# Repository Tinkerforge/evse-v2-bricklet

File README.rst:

EVSE Bricklet 2.0
=================

This Bricklet together with the ESP32 Ethernet Brick and the NFC Bricklet
form the hardware used in the WARP2 Charger.

The Firmware for the EVSE Bricklet 2.0 is also used for the EVSE Bricklet 3.0:
https://github.com/Tinkerforge/evse-v3-bricklet. The hardware version is
run-time detected.

See https://www.warp-charger.com/ for more details about WARP Charger.

This repository contains the firmware source code and the hardware design
files. The documentation generator configs can be found at
https://github.com/Tinkerforge/generators

.. BEGIN WARP REPOSITORIES (managed block, generated from esp32-firmware/repo_overview.rst - do not edit by hand, run update_repo_overview.py instead)

WARP Repositories
-----------------

This is an overview of all repositories that make up the WARP Charger and
WARP Energy Manager ecosystem.

Please report **any** issue concerning WARP hard- or software in the
`esp32-firmware`_ repository, no matter which repository it originates from.

Software
~~~~~~~~

- `esp32-firmware`_ - Source code of the ESP32 firmware shared between all WARP Chargers and Energy Managers

Libraries used by the firmware:

- `tfjson`_ - SAX style JSON serializer and deserializer
- `tfnetwork`_ - Modbus TCP server and client implementation
- `tfocpp`_ - OCPP 1.6 implementation
- `tftools`_ - Miscellaneous tools and helpers

Remote access:

- `esp32-remote-access`_ - Source code of the my.warp-charger.com remote access server

Documentation, tools and integrations:

- `warp-charger`_ - Source code of (docs.)warp-charger.com and the printed manual, released firmwares, datasheets and documents, as well as some tools and hardware design files
- `api.warp-charger.com`_ - Serves APIs that are used by WARP Chargers to obtain relevant public information like day ahead prices
- `vislog.warp-charger.com`_ - Visualizes WARP Charger logs and EVSE debug protocols
- `dbus-warp-charger`_ - Integrates WARP Chargers into a Victron Energy Venus OS device (e.g. Cerbo GX)

WARP Charger Hardware
~~~~~~~~~~~~~~~~~~~~~~

WARP4 Charger
"""""""""""""

*Current charger generation.*

- `warp-esp32-ethernet-v2-brick`_ - Hardware design files of the WARP ESP32 Ethernet Brick 2.0
- `warp-esp32-ethernet-v2-co-bricklet`_ - Firmware source code of the WARP ESP32 Ethernet 2.0 Co Bricklet (co-processor)
- `evse-v4-bricklet`_ - Hardware design files of the EVSE 4.0 Bricklet (firmware shared with the EVSE 2.0 Bricklet)
- `nfc-bricklet`_ - Firmware source code and hardware design files of the NFC Bricklet

WARP3 Charger
"""""""""""""

- `warp-esp32-ethernet-brick`_ - Hardware design files of the WARP ESP32 Ethernet Brick
- `evse-v3-bricklet`_ - Hardware design files of the EVSE 3.0 Bricklet (firmware shared with the EVSE 2.0 Bricklet)
- `nfc-bricklet`_ - Firmware source code and hardware design files of the NFC Bricklet

WARP2 Charger
"""""""""""""

- `esp32-ethernet-brick`_ - Hardware design files of the ESP32 Ethernet Brick
- `evse-v2-bricklet`_ - Firmware source code and hardware design files of the EVSE 2.0 Bricklet
- `nfc-bricklet`_ - Firmware source code and hardware design files of the NFC Bricklet

WARP1 Charger
"""""""""""""

- `esp32-brick`_ - Hardware design files of the ESP32 Brick
- `evse-bricklet`_ - Firmware source code and hardware design files of the EVSE Bricklet
- `rs485-bricklet`_ - Firmware source code and hardware design files of the RS485 Bricklet

WARP Energy Manager Hardware
~~~~~~~~~~~~~~~~~~~~~~~~~~~~~~

WARP Energy Manager 2.0
"""""""""""""""""""""""

*Current energy manager generation.*

- `esp32-ethernet-brick`_ - Hardware design files of the ESP32 Ethernet Brick
- `warp-energy-manager-v2-bricklet`_ - Firmware source code and hardware design files of the WARP Energy Manager 2.0 Bricklet
- `warp-front-panel-bricklet`_ - Firmware source code and hardware design files of the WARP Front Panel Bricklet

WARP Energy Manager 1.0
"""""""""""""""""""""""

- `esp32-ethernet-brick`_ - Hardware design files of the ESP32 Ethernet Brick
- `warp-energy-manager-bricklet`_ - Firmware source code and hardware design files of the WARP Energy Manager Bricklet

Forked/patched projects
~~~~~~~~~~~~~~~~~~~~~~~~~

- `arduino-esp32`_
- `esp32-arduino-libs`_
- `WireGuard-ESP32-Arduino`_

.. Link targets: One definition per repository, keep in sync with the lists above.

.. _esp32-firmware: https://github.com/Tinkerforge/esp32-firmware
.. _tfjson: https://github.com/Tinkerforge/tfjson
.. _tfnetwork: https://github.com/Tinkerforge/tfnetwork
.. _tfocpp: https://github.com/Tinkerforge/tfocpp
.. _tftools: https://github.com/Tinkerforge/tftools
.. _esp32-remote-access: https://github.com/Tinkerforge/esp32-remote-access
.. _warp-charger: https://github.com/Tinkerforge/warp-charger
.. _api.warp-charger.com: https://github.com/Tinkerforge/api.warp-charger.com
.. _vislog.warp-charger.com: https://github.com/Tinkerforge/vislog.warp-charger.com
.. _dbus-warp-charger: https://github.com/Tinkerforge/dbus-warp-charger
.. _warp-esp32-ethernet-v2-brick: https://github.com/Tinkerforge/warp-esp32-ethernet-v2-brick
.. _warp-esp32-ethernet-v2-co-bricklet: https://github.com/Tinkerforge/warp-esp32-ethernet-v2-co-bricklet
.. _evse-v4-bricklet: https://github.com/Tinkerforge/evse-v4-bricklet
.. _nfc-bricklet: https://github.com/Tinkerforge/nfc-bricklet
.. _warp-esp32-ethernet-brick: https://github.com/Tinkerforge/warp-esp32-ethernet-brick
.. _evse-v3-bricklet: https://github.com/Tinkerforge/evse-v3-bricklet
.. _esp32-ethernet-brick: https://github.com/Tinkerforge/esp32-ethernet-brick
.. _evse-v2-bricklet: https://github.com/Tinkerforge/evse-v2-bricklet
.. _esp32-brick: https://github.com/Tinkerforge/esp32-brick
.. _evse-bricklet: https://github.com/Tinkerforge/evse-bricklet
.. _rs485-bricklet: https://github.com/Tinkerforge/rs485-bricklet
.. _warp-energy-manager-v2-bricklet: https://github.com/Tinkerforge/warp-energy-manager-v2-bricklet
.. _warp-front-panel-bricklet: https://github.com/Tinkerforge/warp-front-panel-bricklet
.. _warp-energy-manager-bricklet: https://github.com/Tinkerforge/warp-energy-manager-bricklet
.. _arduino-esp32: https://github.com/Tinkerforge/arduino-esp32
.. _esp32-arduino-libs: https://github.com/Tinkerforge/esp32-arduino-libs
.. _WireGuard-ESP32-Arduino: https://github.com/Tinkerforge/WireGuard-ESP32-Arduino

.. END WARP REPOSITORIES

Repository Content
------------------

software/:
 * examples/: Examples for all supported languages
 * build/: Compiled files
 * src/: Source code of firmware
 * Makefile: Makefile to build project

hardware/:
 * Contains KiCad project files and additionally schematics as PDF

datasheets/:
 * Contains datasheets for sensors and complex ICs that are used

Hardware
--------

The hardware is designed with the open source EDA Suite KiCad
(http://www.kicad.org). Before you are able to open the files,
you have to install the Tinkerforge kicad-libraries
(https://github.com/Tinkerforge/kicad-libraries). You can either clone
them directly in hardware/ or clone them in a separate folder and
symlink them into hardware/
(ln -s kicad_path/kicad-libraries project_path/hardware). After that you
can open the .pro file in hardware/ with KiCad and from there view and
modify the schematics and the PCB layout.

Software
--------

If you want to do your own Brick/Bricklet firmware development we highly
recommend that you use our build environment setup script and read the
tutorial (https://www.tinkerforge.com/en/doc/Tutorials/Tutorial_Build_Environment/Tutorial.html).

To compile the C code we recommend you to install the newest GNU Arm Embedded
Toolchain (https://launchpad.net/gcc-arm-embedded/+download).
You also need to install bricklib2 (https://github.com/Tinkerforge/bricklib2).

You can either clone it directly in software/src/ or clone it in a
separate folder and symlink it into software/src/
(ln -s bricklib_path/bricklib2 project_path/software/src/). Finally make sure to
have CMake installed (http://www.cmake.org/cmake/resources/software.html).

After that you can build the firmware by invoking make in software/.
The firmware (.zbin) can then be found in software/build/ and uploaded
with brickv (click button "Flashing" on start screen).

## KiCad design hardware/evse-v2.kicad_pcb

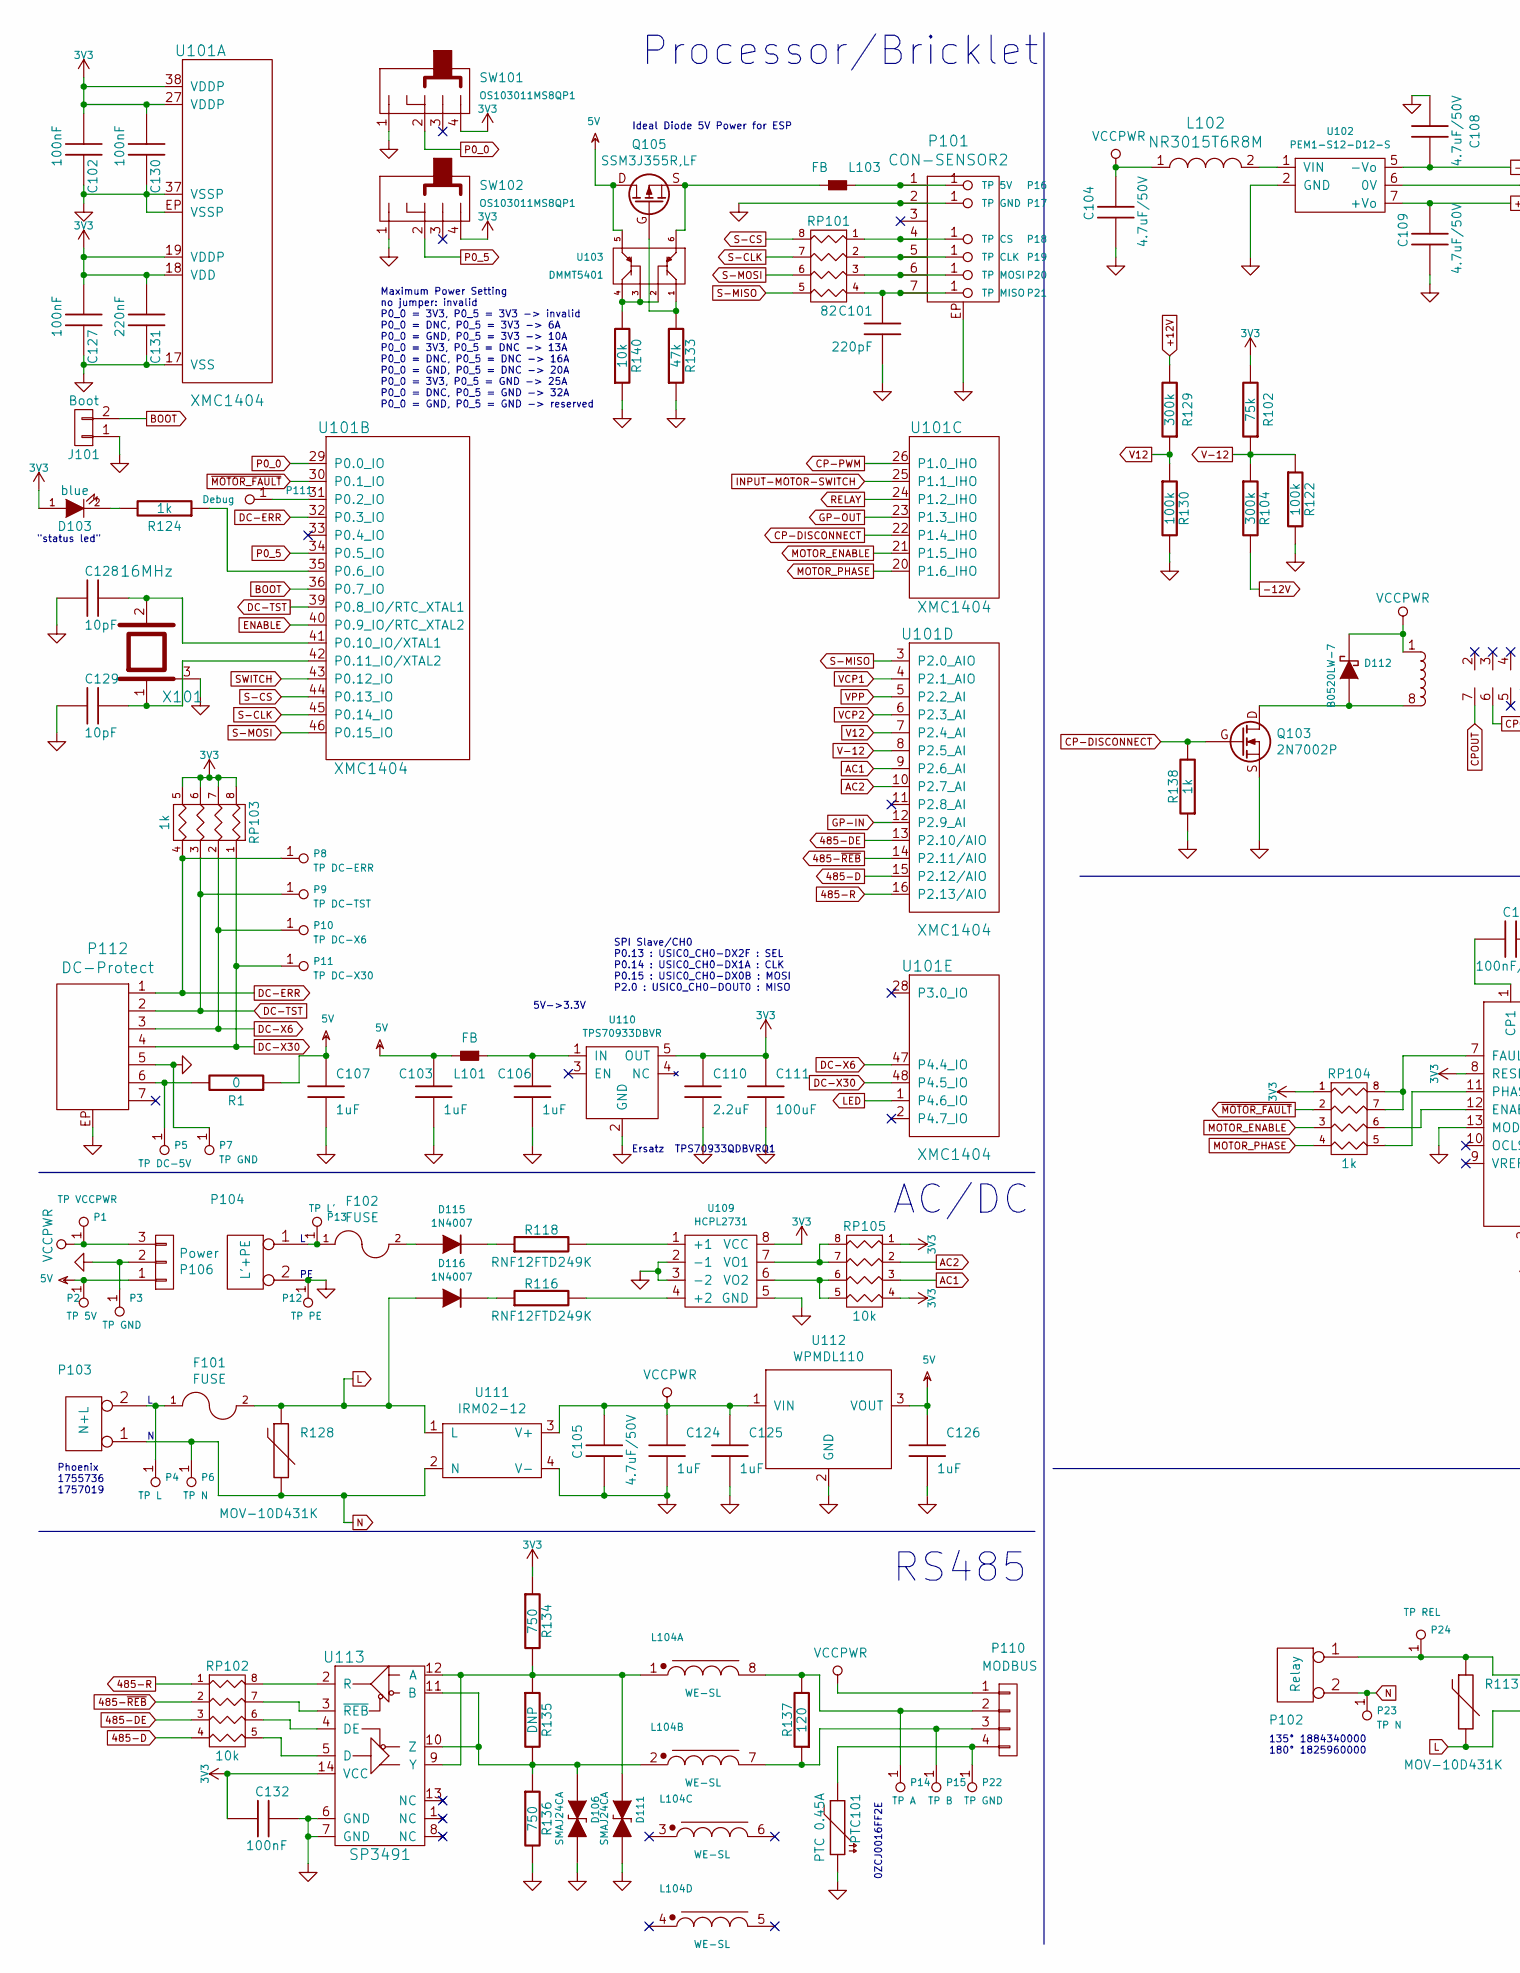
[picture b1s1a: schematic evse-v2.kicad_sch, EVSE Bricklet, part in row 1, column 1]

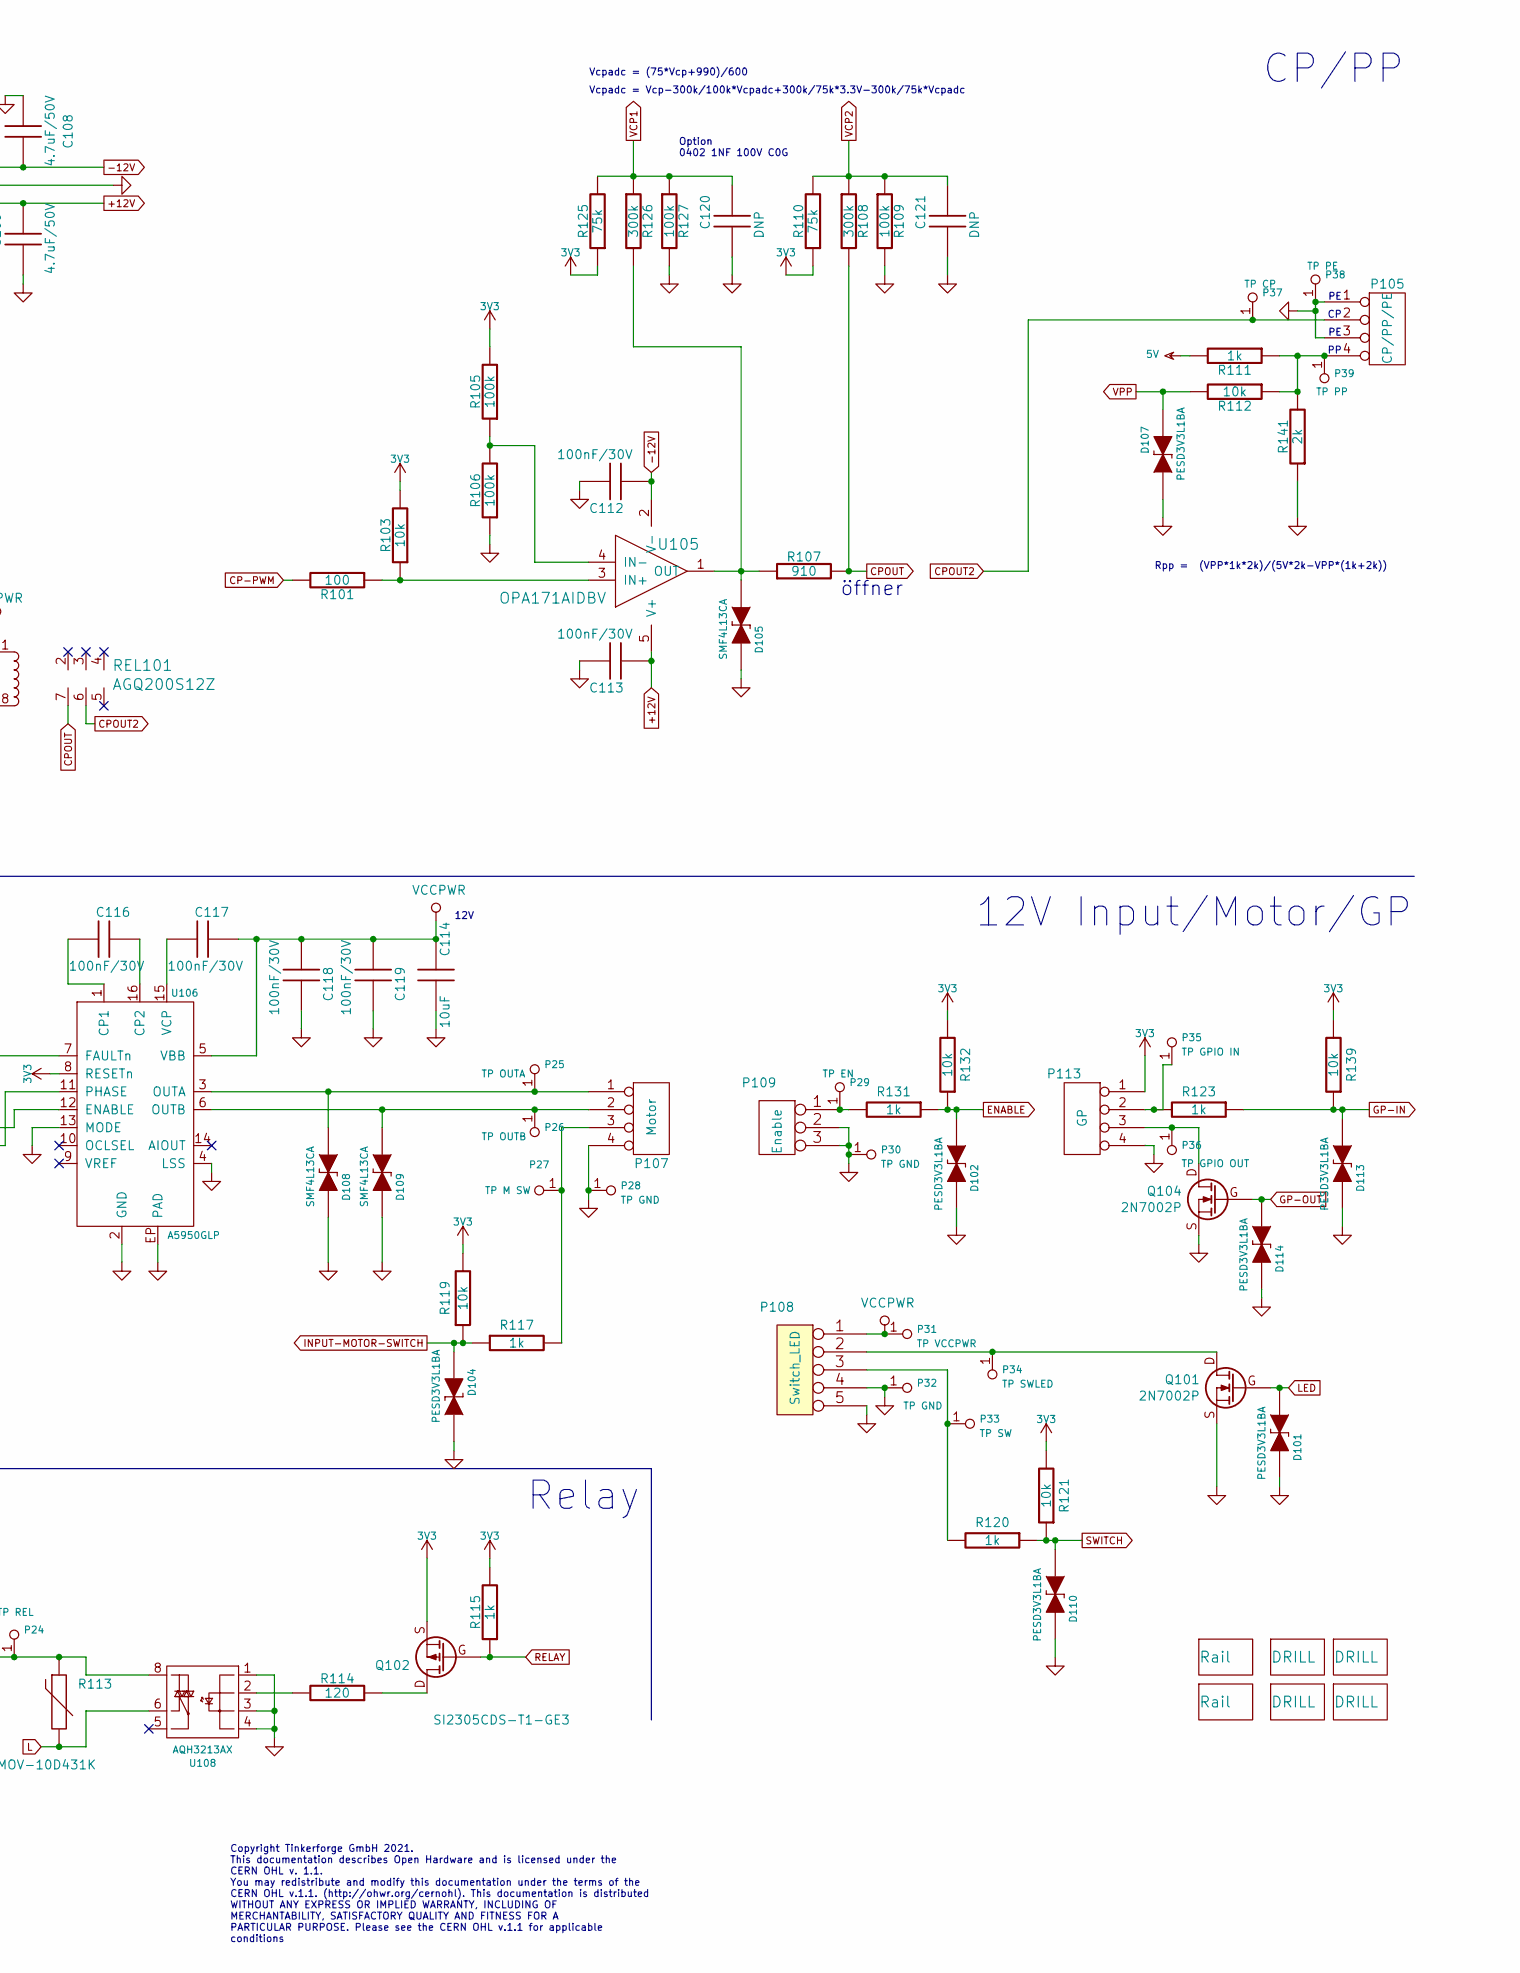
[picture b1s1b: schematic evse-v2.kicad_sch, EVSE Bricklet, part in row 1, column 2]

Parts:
A101, A102, A103, A104: DRILL; DRILL_NP_35
A105, A106: Rail; din-rail-mount
C101: 220pF; C0402F
C102, C127, C130, C132: 100nF; C0603F
C103, C106, C107, C124, C125, C126: 1uF; C0603F
C104, C105, C108, C109: 4.7uF/50V; C1206
C110: 2.2uF; C0603F
C111: 100uF; C1210
C112, C113, C116, C117, C118, C119: 100nF/30V; C0603F
C114: 10uF; C1206
C120, C121: DNP; C0402F
C128, C129: 10pF; C0603F
C131: 220nF; C0603F
D101, D102, D104, D107, D110, D113, D114: ‎PESD3V3L1BA; SOD-323
D103: blue; D0603F
D105, D108, D109: SMF4L13CA; SOD-123FL
D106, D111: SMAJ24CA; DO-214AC
D112: B0520LW-7; SOD-123
D115, D116: 1N4007; DO-41
F101, F102: FUSE; Fuse-Holder-5x20
J101: Boot; SolderJumper
L101, L103: FB; R0603F
L102: NR3015T6R8M; NR3030
L104: WE-SL
P1, P31: TP VCCPWR; TSTPT
P2, P16: TP 5V; TSTPT
P3, P7, P17, P22, P28, P30, P32: TP GND; TSTPT
P4: TP L; TSTPT
P5: TP DC-5V; TSTPT
P6, P23: TP N; TSTPT
P8: TP DC-ERR; TSTPT
P9: TP DC-TST; TSTPT
P10: TP DC-X6; TSTPT
P11: TP DC-X30; TSTPT
P12, P38: TP PE; TSTPT
P13: TP L'; TSTPT
P14: TP A; TSTPT
P15: TP B; TSTPT
P18: TP CS; TSTPT
P19: TP CLK; TSTPT
P20: TP MOSI; TSTPT
P21: TP MISO; TSTPT
P24: TP REL; TSTPT
P25: TP OUTA; TSTPT
P26: TP OUTB; TSTPT
P27: TP M SW; TSTPT
P29: TP EN; TSTPT
P33: TP SW; TSTPT
P34: TP SWLED; TSTPT
P35: TP GPIO IN; TSTPT
P36: TP GPIO OUT; TSTPT
P37: TP CP; TSTPT
P39: TP PP; TSTPT
P101: CON-SENSOR2; CON-SENSOR2_180
P102: Relay; LSF-SMT-500-02-135
P103: N+L; wm_2491620000
P104: L'+PE; wm_2491620000
P105: CP/PP/PE; OQ_4P_Vertical
P106: Power; JST-PH-3-THT
P107: Motor; JST-PH-4-THT
P108: Switch_LED; JST-PH-5-THT
P109: Enable; JST-PH-3-THT
P110: MODBUS; JST-PH-4-THT
P111: Debug; DEBUG_PAD
P112: DC-Protect; CON-SENSOR2_180
P113: GP; JST-PH-4-THT
PTC101: PTC 0.45A; C1206
Q101, Q103, Q104: 2N7002P; SOT23GDS
Q102: SI2305CDS-T1-GE3; SOT23GDS
Q105: SSM3J355R,LF; SOT23GDS
R1: 0; R1210
R101: 100; R0603F
R102, R110, R125: 75k; R0603F
R103, R112, R119, R121, R132, R139, R140: 10k; R0603F
R104, R108, R126, R129: 300k; R0603F
R105, R106, R109, R122, R127, R130: 100k; R0603F
R107: 910; R0603F
R111, R115, R117, R120, R123, R124, R131, R138: 1k; R0603F
R113, R128: MOV-10D431K; VAR_10mm
R114, R137: 120; R0805E
R116, R118: RNF12FTD249K; RNF12-2
R133: 47k; R0603F
R134, R136: 750; R0603F
R135: DNP; R0603F
R141: 2k; R0603F
REL101: AGQ200S12Z; AGQ2X0
RP101: 82; 4X0402
RP102: 10k; 0603X4
RP103, RP104: 1k; 4X0603
RP105: 10k; 4X0603
SW101, SW102: OS103011MS8QP1
U101: XMC1404; QFN48-EP2
U102: PEM1-S12-D12-S; PEM1S
U103: DMMT5401; SOT26
U105: OPA171AIDBV; SOT23-5
U106: A5950GLP; TSSOP16_EP
U108: AQH3213AX; AQ-H
U109: HCPL2731; DIP-8
U110: TPS70933DBVR; SOT23-5
U111: IRM02-12; IRM02
U112: WPMDL110
U113: SP3491; SOIC-14_3.9x8.7mm_Pitch1.27mm
X101: 16MHz; CRYSTAL_3225

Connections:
3V3: C102.1, C110.1, C111.1, C127.1, C130.1, C131.1, C132.2, D103.1 (A), P113.1, Q102.S, R102.2, R103.2, R105.2, R110.1, R115.2, R119.2, R121.2, R125.1, R132.2, R134.1, R139.2, RP103.5 (R4), RP103.6 (R3), RP103.7 (R2), RP103.8 (R1), RP104.1, RP105.1, RP105.4, SW101.4, SW102.4, U101.18 (VDD), U101.19 (VDDP), U101.27 (VDDP), U101.38 (VDDP), U106.8 (RESETn), U109.8 (VCC), U110.5 (OUT), U113.14 (VCC)
5V: C103.1, C107.1, C126.1, L101.2, P2.1, P106.1, Q105.D, R1.1, R111.2, U103.5, U112.3 (VOUT)
485-D: RP102.4, U101.15 (P2.12/AIO)
485-DE: RP102.3, U101.13 (P2.10/AIO)
485-R: RP102.1, U101.16 (P2.13/AIO)
485-~REB: RP102.2, U101.14 (P2.11/AIO)
+12V: C109.1, C113.2, R129.2, U102.7 (+Vo), U105.5 (V+)
-12V: C108.2, C112.2, R104.2, U102.5 (-Vo), U105.2 (V-)
AC1: RP105.3, U101.9 (P2.6_AI)
AC2: RP105.2, U101.10 (P2.7_AI)
BOOT: J101.2, U101.36 (P0.7_IO)
CP-DISCONNECT: Q103.G, R138.2, U101.22 (P1.4_IHO)
CP-PWM: R101.2, U101.26 (P1.0_IHO)
CPOUT: R107.2, R108.2, REL101.7
CPOUT2: P37.1, P105.2, REL101.6
DC-ERR: P8.1, P112.1, RP103.4, U101.32 (P0.3_IO)
DC-TST: P9.1, P112.2, RP103.3, U101.39 (P0.8_IO/RTC_XTAL1)
DC-X6: P10.1, P112.3, RP103.2, U101.47 (P4.4_IO)
DC-X30: P11.1, P112.4, RP103.1, U101.48 (P4.5_IO)
ENABLE: D102.1 (A), R131.1, R132.1, U101.40 (P0.9_IO/RTC_XTAL2)
GND: C101.2, C102.2, C103.2, C104.2, C105.2, C106.2, C107.2, C108.1, C109.2, C110.2, C111.2, C112.1, C113.1, C114.2, C118.1, C119.1, C120.2, C121.2, C124.2, C125.2, C126.2, C127.2, C128.2, C129.2, C130.2, C131.2, C132.1, D101.2 (K), D102.2 (K), D104.1 (A), D105.2 (K), D106.2 (K), D107.1 (A), D108.2 (K), D109.2 (K), D110.2 (K), D111.2 (K), D113.2 (K), D114.2 (K), J101.1, P3.1, P7.1, P12.1, P17.1, P28.1, P30.1, P32.1, P38.1, P101.2, P101.EP, P104.2 (PM), P105.1, P105.3, P106.2, P107.4, P108.4, P108.5, P109.2 (PM), P109.3, P112.5, P112.EP, P113.4, PTC101.2, Q101.S, Q103.S, Q104.S, R106.1, R109.2, R122.2, R127.2, R130.2, R133.1, R136.2, R138.1, R140.1, R141.1, SW101.1, SW102.1, U101.17 (VSS), U101.37 (VSSP), U101.EP (VSSP), U102.2 (GND), U102.6 (0V), U106.2 (GND), U106.4 (LSS), U106.13 (MODE), U106.EP (PAD), U108.1, U108.3, U108.4, U109.2 (-1), U109.3 (-2), U109.5 (GND), U110.2 (GND), U111.4 (V-), U112.2 (GND), U113.6 (GND), U113.7 (GND), X101.3
GP-IN: D113.1 (A), R123.1, R139.1, U101.12 (P2.9_AI)
GP-OUT: D114.1 (A), Q104.G, U101.23 (P1.3_IHO)
INPUT-MOTOR-SWITCH: D104.2 (K), R117.1, R119.1, U101.25 (P1.1_IHO)
L: D116.1 (A), F101.2, R113.2, R128.1, U108.6, U111.1 (L)
LED: D101.1 (A), Q101.G, U101.1 (P4.6_IO)
MOTOR_ENABLE: RP104.3, U101.21 (P1.5_IHO)
MOTOR_PHASE: RP104.4, U101.20 (P1.6_IHO)
N: P6.1, P23.1, P102.2 (PM), P103.1, R128.2, U111.2 (N)
unnamed: C101.1, P21.1, P101.7, RP101.4
unnamed: C106.1, L101.1, U110.1 (IN)
unnamed: C116.1, U106.16 (CP2)
unnamed: C116.2, U106.1 (CP1)
unnamed: C117.2, U106.15 (VCP)
unnamed: C128.1, U101.41 (P0.10_IO/XTAL1), X101.2
unnamed: C129.1, U101.42 (P0.11_IO/XTAL2), X101.1
unnamed: D103.2 (K), R124.2
unnamed: D105.1 (A), R107.1, R126.2, U105.1 (OUT)
unnamed: D106.1 (A), L104.2, R135.2, R136.1, U113.10 (Z), U113.11 (B)
unnamed: D108.1 (A), P25.1, P107.1, U106.3 (OUTA)
unnamed: D109.1 (A), P26.1, P107.2, U106.6 (OUTB)
unnamed: D111.1 (A), L104.1, R134.2, R135.1, U113.9 (Y), U113.12 (A)
unnamed: D112.1 (A), Q103.D, REL101.8
unnamed: D115.1 (A), F102.2
unnamed: D115.2 (K), R118.1
unnamed: D116.2 (K), R116.1
unnamed: F101.1, P4.1, P103.2 (PM)
unnamed: F102.1, P13.1, P104.1
unnamed: L102.2, U102.1 (VIN)
unnamed: L103.1, Q105.S, U103.6
unnamed: L103.2, P16.1, P101.1
unnamed: L104.7, P15.1, P110.3, R137.1
unnamed: L104.8, P14.1, P110.2, R137.2
unnamed: P18.1, P101.4, RP101.1
unnamed: P19.1, P101.5, RP101.2
unnamed: P20.1, P101.6, RP101.3
unnamed: P24.1, P102.1, R113.1, U108.8
unnamed: P39.1, P105.4, R111.1, R112.1, R141.2
unnamed: P27.1, P107.3, R117.2
unnamed: P34.1, P108.2, Q101.D
unnamed: P33.1, P108.3, R120.2
unnamed: P29.1, P109.1, R131.2
unnamed: P22.1, P110.4, PTC101.1
unnamed: P111.1, U101.31 (P0.2_IO)
unnamed: P5.1, P112.6, R1.2
unnamed: P35.1, P113.2, R123.2
unnamed: P36.1, P113.3, Q104.D
unnamed: Q102.D, R114.1
unnamed: Q105.G, R133.2, U103.1
unnamed: R101.1, R103.1, U105.3 (IN+)
unnamed: R105.1, R106.2, U105.4 (IN-)
unnamed: R114.2, U108.2
unnamed: R116.2, U109.4 (+2)
unnamed: R118.2, U109.1 (+1)
unnamed: R124.1, U101.35 (P0.6_IO)
unnamed: R140.2, U103.2, U103.3, U103.4
unnamed: RP102.5 (R4), U113.5 (D)
unnamed: RP102.6 (R3), U113.4 (DE)
unnamed: RP102.7 (R2), U113.3 (~REB)
unnamed: RP102.8 (R1), U113.2 (R)
unnamed: RP104.5 (R4), U106.11 (PHASE)
unnamed: RP104.6 (R3), U106.12 (ENABLE)
unnamed: RP104.7 (R2), RP104.8 (R1), U106.7 (FAULTn)
unnamed: RP105.5 (R4), RP105.6 (R3), U109.6 (VO2)
unnamed: RP105.7 (R2), RP105.8 (R1), U109.7 (VO1)
P0_0: SW101.2, U101.29 (P0.0_IO)
P0_5: SW102.2, U101.34 (P0.5_IO)
RELAY: Q102.G, R115.1, U101.24 (P1.2_IHO)
S-CLK: RP101.7 (R2), U101.45 (P0.14_IO)
S-CS: RP101.8 (R1), U101.44 (P0.13_IO)
S-MISO: RP101.5 (R4), U101.3 (P2.0_AIO)
S-MOSI: RP101.6 (R3), U101.46 (P0.15_IO)
SWITCH: D110.1 (A), R120.1, R121.1, U101.43 (P0.12_IO)
V12: R129.1, R130.1, U101.7 (P2.4_AI)
V-12: R102.1, R104.1, R122.1, U101.8 (P2.5_AI)
VCC: C104.1, C105.1, C114.1, C117.1, C118.2, C119.2, C124.1, C125.1, D112.2 (K), L102.1, P1.1, P31.1, P106.3, P108.1, P110.1, REL101.1, U106.5 (VBB), U111.3 (V+), U112.1 (VIN)
VCP1: C120.1, R125.2, R126.1, R127.1, U101.4 (P2.1_AIO)
VCP2: C121.1, R108.1, R109.1, R110.2, U101.6 (P2.3_AI)
VPP: D107.2 (K), R112.2, U101.5 (P2.2_AI)
~MOTOR_FAULT: RP104.2, U101.30 (P0.1_IO)

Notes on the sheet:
Phoenix 1755736 1757019
öffner
Ersatz TPS70933QDBVRQ1
0ZCJ0016FF2E
Ideal Diode 5V Power for ESP
12V
CP/PP
Rpp = (VPP*1k*2k)/(5V*2k-VPP*(1k+2k))
Option 0402 1NF 100V C0G
RS485
Relay
Vcpadc = (75*Vcp+990)/600
12V Input/Motor/GP
"status led"
Processor/Bricklet
AC/DC
135° 1884340000 180° 1825960000
Copyright Tinkerforge GmbH 2021. This documentation describes Open Hardware and is licensed under the CERN OHL v. 1.1. You may redistribute and modify this documentation under the terms of the CERN OHL v.1.1. (http://ohwr.org/cernohl). This documentation is distributed WITHOUT ANY EXPRESS OR IMPLIE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
SPI Slave/CH0 P0.13 : USIC0_CH0-DX2F : SEL P0.14 : USIC0_CH0-DX1A : CLK P0.15 : USIC0_CH0-DX0B : MOSI P2.0 : USIC0_CH0-DOUT0 : MISO
5V->3.3V
Vcpadc = Vcp-300k/100k*Vcpadc+300k/75k*3.3V-300k/75k*Vcpadc
Maximum Power Setting no jumper: invalid P0_0 = 3V3, P0_5 = 3V3 -> invalid P0_0 = DNC, P0_5 = 3V3 -> 6A P0_0 = GND, P0_5 = 3V3 -> 10A P0_0 = 3V3, P0_5 = DNC -> 13A P0_0 = DNC, P0_5 = DNC -> 16A P0_0 = GND, P0_5 = DNC -> 20A P0_0 = 3V3, P0_5 = GND -> 25A P0_0 = DNC, P0_5 = GND -> 32A P0_0 = GND, P0_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

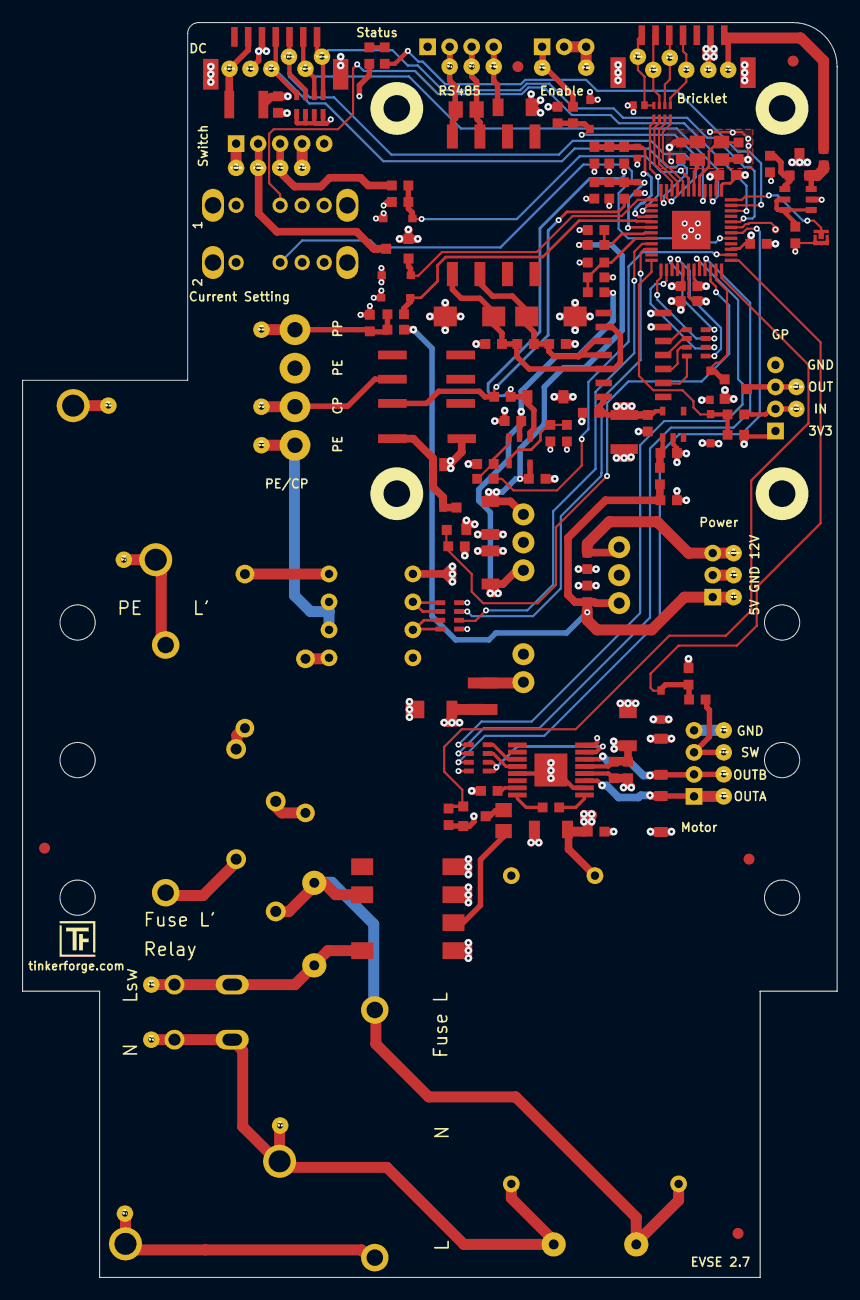
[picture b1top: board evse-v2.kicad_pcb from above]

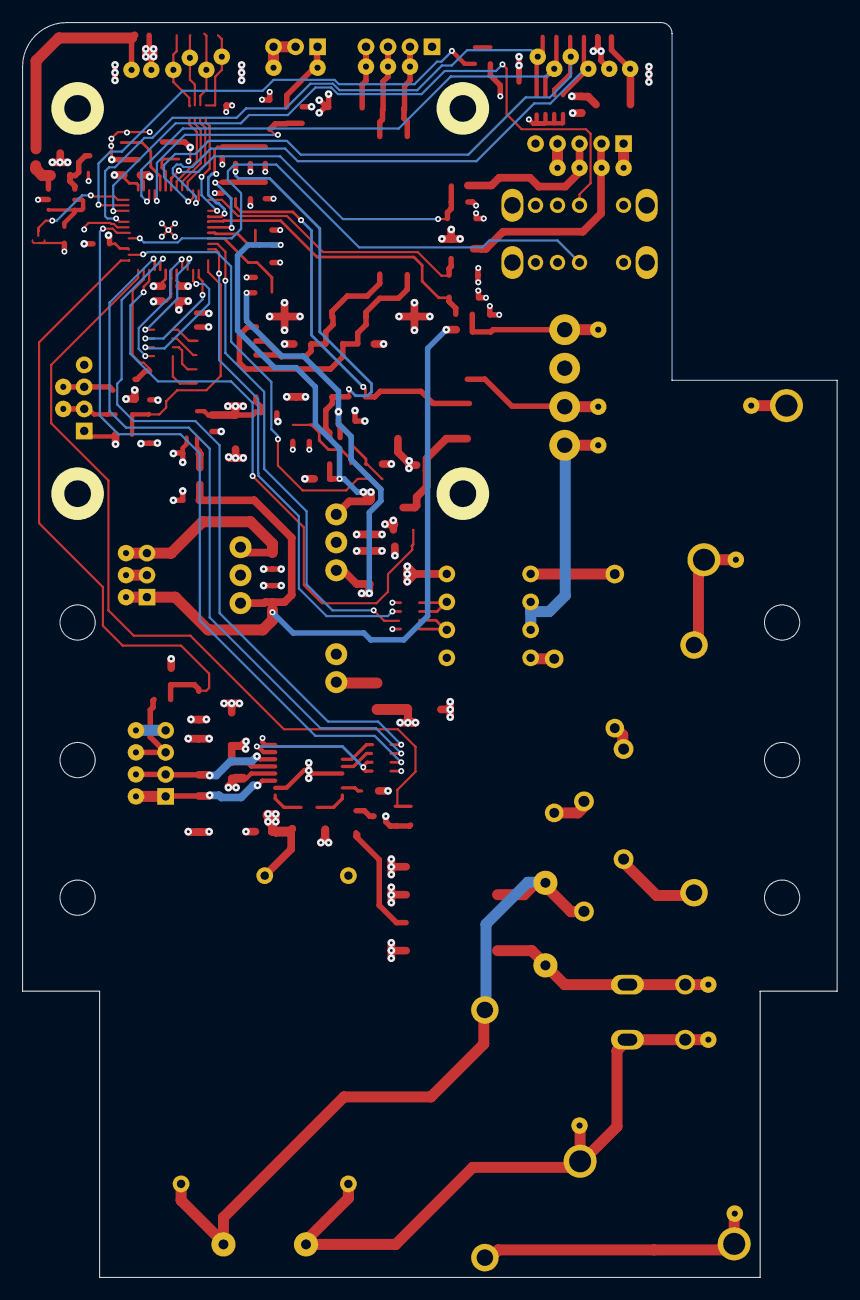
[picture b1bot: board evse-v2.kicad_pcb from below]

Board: 4 copper layers, 74.0 x 114.0 mm, 183 parts (2 on the bottom side), 100 nets.

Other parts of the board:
Fiducial_Mark: VAL**; Fiducial_Mark
Fiducial_Mark#2, Fiducial_Mark#3, Fiducial_Mark#4, Fiducial_Mark#5: VAL**; Fiducial_Mark

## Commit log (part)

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2021-09-29 Add some wait time in case of unexpected error
    This gives the energy meter some time to recover
2021-09-29 change rs485 bias resistor values
2021-10-06 Increment version and add changelog for v2.0.4
2021-10-12 Add TimeSinceCPPWMChange parameter to low level state getter
2021-10-12 Only update pwm time if we change from or to 100%
2021-10-13 Add ChargeTime parameter to low level state getter
2021-10-15 Add GetAllDataX API
    For internal use in WARP Charger only
2021-10-20 Update changelog
2021-10-27 Add date and rev
2021-11-02 Use 180V as threshold for connected phase
2021-11-02 A phase can only be active if it is connected
2021-12-03 Add rev for 2.0.6
2022-01-10 Add rev for 2.0.7
2022-01-17 Make sure incomming/outgoing cable slots are set correctly
2022-01-17 return HANDLE_MESSAGE_RESPONSE_NEW_MESSAGE for getter
2022-01-17 Add slot support to full test
2022-01-17 Always reset button slot on disconnect
    If clear on disconnect is true it will be overwritten with 0 directly aftwards
2022-01-17 Move was_pressed led logic to button state machine
2022-01-18 Increase version, add changelog
2022-01-18 Make full test compatible to new API names
2022-01-24 Add charging slot setter per parameter
2022-01-26 Add rev for 2.0.1
2022-02-21 Improve all data API segmentation
    Assume that the managed mode is configured in slot 7
    and apply the legacy configuration to it
2022-03-28 Add rev for 2.1.2
2022-04-26 Add support for SDM72V2
2022-05-06 Improve button start/stop logic
2022-05-09 Add PDF schematic
2022-06-07 Make sure to never start charging when button is pressed
    and during energy meter detection use SDM630 as default
2022-06-09 Fix bug with meter type detection for WARP2 Charger Smart
    meter type was detected as SDM630, even when no meter was connected...
2022-06-28 Improve resolution of duty cycle calculation
    We now have a max current resolution of 1.25mA
2022-07-04 Add minimum time of 30s between error state E/F and next activation of contactor
2022-07-06 Add license files.
2022-07-06 Implement reset for button-press-boot-time
2022-08-22 FIX bug in PP/PE voltage calculation
2022-08-23 Make sure set_control_pilot_configuration returns connected value
2022-08-25 Imprive diode error check
2022-10-21 evse with testpoints
2022-11-15 Make sure that control pilot disconnect does not zero user slot on accident
2022-11-16 Add additional master communication watchdog
2022-11-16 Makae sure communication watchdog time is initialized with 0
2022-12-06 Fix typo
2022-12-06 Add and implement API for get/set boost modus
2022-12-15 Rename Modus -> Mode
2022-12-22 Properly detect B1/B2 transition for cp disconnect handling
2023-01-13 Make sure to set system type back to false
2023-01-19 Set contactor check invalid counter in case of emergency contactor shutdown (dc error)
2023-01-20 Version 2.6: Upadated to Kicad 6. Changed L103 to 0 Ohm resistor.
2023-02-24 Add changes and date to changelog
2023-02-24 Add units to test output
2023-03-15 Use max current input configuration only when input is active (high or low)
2023-03-17 Add ref and date for release 2.1.11
2023-03-23 Remove development hint, add some details
2023-04-27 Add blink led indicator code 2001-2010
    for custom error code with 1-10 "blink amount"
2023-04-28 Fix external blink detection (new blink pattern is new activation)
2023-05-02 change varistor
2023-06-05 Add support for set_gp_output function
    This function sets the output without changing the bootup-default
2023-06-13 Avoid collision betweing logf logging.h and math.h
    On some systems, math.h declares a function named logf(float) to calculate
    the natural logarithm of a float number. bricklib2's logging.h defines
    a macro called logf(...) to log fatal errors. The hack below renames the
    unused logf from math.h to logf_math to avoid colliding with logf from
    logging.h.
2023-06-15 Move meter functionality to bricklib2/warp
    This is now shared with WARP Energy Manager Bricklet
2023-06-19 Fix relay inversion configuration
2023-06-21 Add change in bricklib to changelog
2023-06-28 Don't check for DC fault when contactor is turned off
2023-07-07 Add additional hysteresis for contactor
2023-08-21 Add CONTACTOR_PIN define for bricklib2 compatibility
    Some changes of the WARP3 branch did leak into the bricklib2.
    For now we just use both defines here (RELAY and CONTACTOR).
    Later when we merge the WARP3 branch the RELAY define will be removed.
2023-08-22 Fix typo in changelog
2023-10-27 Fix errors in LED CCU8 configuration
2023-10-27 Improve EVSE version detection
2023-10-27 Initial V3 support
2023-10-27 Use new unified meter implementation from bricklib2
2023-10-27 Increase version to 2.2.0 for WARP3 support chages
2023-10-31 Add additional debug information to dc fault state
2023-10-31 Add TMP1075N implementation
    This is still WIP and currently unused.
2023-11-03 Add automatic phase switching through API
2023-11-06 Add support for 20mA AC fault current detection
    Note: This does not replace an AC RCD!
2023-11-09 Fix parameter sequence copy+paste error
2023-11-10 Add EVSE V3 GPIO
2023-11-10 Add support for YTL DEM4A meter
2023-11-14 Fix I2C address
2023-11-14 Read more then the expected value
    This ensures that the buffer is always empties if something goes wrong
2023-11-14 Enable TMP1075N
2023-11-15 Increase dc fault debounce to 50ms
2023-12-11 Use same parameters for AllData as for the Energy Meter function
2023-12-19 Fix third check during dc fault calibration
    In third check both x6 and x30 need to be low. Before we only checked
    if at least one of them is low.
2023-12-21 LED API now has higher priority than breathing LED during charging
2024-01-10 Remove jumper config double check
2024-01-10 Every error state results in a charger state
2024-01-23 Make sure that the diode check is only run if at least one negative PWM value has been measured
    Otherwise, if the wallbox is restartet during a charging session,
    it is possible that the wallbox erroneously goes into an diode
    error for a few ms after startuo.
2024-01-29 Fix bug in DC fault detection debounce
2024-02-14 Add support for EVSE V3 jumper configuration
2024-02-16 Add EVSE V3 testing script
2024-02-16 Turn LED completely on
2024-02-16 Use correct GPIO
2024-02-16 adapt v3 test to changes in test lib
2024-02-23 Improve timeout for phase control contactor off state
2024-02-23 Don't wait for car to stop charging in phase control state machine
    this is already done ine evse_set_output internally
2024-02-28 Add support for auto-switch to 1-phase
2024-03-05 Do not check hardware version
2024-03-05 Add phase info parameter
    The info parameter is set to 1 if 1-phase was forced by auto-switch
2024-03-14 Fix LED colors for nag and error.
    Setting the error hue to orange was ignored anyway.
2024-03-14 Use set h/s/v value instead of current
2024-03-20 Add API to configure connected phases
    this configuration is persistent on reboot
2024-03-28 Use 4.2kW as default for shutdown input (not 4.3kW)
2024-04-04 Add date and rev for 2.2.3
2024-04-08 Add initial changelog entry for 2.2.4
2024-05-21 Make sure charging is stopped when button is pressed
    while wallbox is in IEC61851 state B2 ans started
    when wallbox is in IEC61851 state B1 if configured accordingly
2024-05-24 Add ref and date for 2.2.4
2024-09-05 Make sure charging time is zeroed when car does not wake up again after phase change
2024-09-19 Make sure charging time is always started when IEC61851 state changes to C
2024-11-05 Increase version
2024-11-05 Increase wait time for charge-restart after phase change from 3s to 10s
2024-11-05 If set_control_pilot_disconnect is called, only allow disconnect if contactor is not active (and iec61851 state is A or B).
2024-11-18 Fix whitespace
    Normally the Bricklet firmwares use tabs. Lots of spaces have
    crept into the EVSE firmware, convert it back to tabs.
2024-11-22 Increase adc ignore results after cp re-connect from 2 counts to 4 counts
2024-11-28 Add ref for 2.2.7
2024-12-05 Set external charging slot to enabled with 32A on first boot of 2.2.8
2024-12-19 If meter is available and only 1 phase is connected to the meter, use this information in phase control
2025-02-05 Add ref for 2.2.9
2025-02-06 Add ref for 2.2.10
2025-03-30 Add initial support for hardware version 4
2025-04-28 Use 30s wait time for autoswitch
2025-04-29 Fix changelog version number mixup
2025-06-03 Add support for longer phase switch wait time in case of EV charger hang-up
    possible fix for problems seen with Polestar chargers
2025-06-09 Add support for DMED341MID7ER meter
2025-06-18 Use pp resistance constants
2025-07-03 Add date and ref for 2.2.12
2025-07-08 Fix "maybe switch under load" flag reset again...
2025-07-16 README: Add repo overview.
2025-07-29 Change ADC integration time from 50ms to 25ms
    we want to have a higher sampling rate to be able to remove
    glitches in sate C -> B transation (see next commits)
2025-07-29 Fix typos
2025-07-29 Change default cp disconnect time for phase switching to 15s
2025-07-29 Ignore ADC results for 550ms after PWM change
    We have seen in several hybrid BMW cars that they have
    a 2700 ohm resistance glitch on the CP line after about
    500ms after a change of the duty cycle....
    We can skip the glitches by ignoring some adc results
    after PWM changes.
2025-07-30 Fix comment
2025-07-31 Add missing use_state_f
2025-08-01 Only use adc_ignore_results if pwm is not turned off
2025-08-01 Add changelog for 2.2.14
2025-08-04 Add rev and date for 2.2.14
2025-08-20 Remove unused v2 lock code
2025-08-20 Remove unused v2 lock function
2025-08-28 Update changelog (changes are mostly in bricklib2)
2025-09-01 Fix CP disconnect race condition that resulted in erroneous charger state
2025-09-04 Add missing negation for disconnected check
2025-09-09 Improve CP disconnect
2025-09-14 Remove unused variables
2025-09-14 Add support for WM3M4C and use restructured meter code
    see bricklib2 for implementation
2025-09-16 Rename MeterRegisterType to use the same name as in esp32 firmware
2025-09-21 Add support for dynamic length meter values
2025-09-24 Fix constness copy+paste errors of strings
2025-09-30 Add Eichrecht transaction handling and API
2025-10-01 Use correct signedness where possible and implicit casts otherwise
2025-10-01 Remove const qualifiers that have no effect
2025-10-01 Add missing break
    The break here is not strictly necessary, since we check for
    time-progress anyway
2025-10-01 Add void for empty functions
2025-10-02 Move measurement_status and signature_status to meter_iskra
    This is now read in the non-eichrecht code as well.
2025-10-07 Don't allow ADC measurements while CP disconnected
2025-10-07 Remove bogus ma != 1000 check
    This check doesn't make sense, it is never true.
2025-10-26 Add API and support for LED enumerator (mode selection by button)
2025-10-30 Fix button_configuration check
2025-10-30 Only increment enumerate value after first button press
2025-10-30 Enumerate LED after first button press if pressed again within 10s
2025-10-30 Set value_change_time to 0 in set_enumerate_value
2025-10-30 Don't allow led to switch from enumerate to off directly
2025-10-31 Improve enumeration value getter
2025-10-31 Only accept new enumerate value if button timer is not running
2025-11-02 Make sure cp can not stay disconnected when ev wakeup is reset
2025-11-03 Add ref and releaes daet for 2.2.17
2025-11-04 Increase firmware version, add changelog entry
2025-11-26 Ignore the ignore_count when cp is disconnected
2026-01-22 Split General Information into Gateway Identification/Serial
    The sizes we need to support for OPCPP (41 and 25 byte) do not fit
    in a single 64 byte tfp message
2026-02-06 Add support for temporary/permanent IEC61851
2026-02-12 communication: Allow 'E' and 'r' in any active state.
    If the meter power cycles while a transaction is running, we have to
    be able to stop this transaction.
2026-02-17 eichrecht: Increase OCMF version to 1.3.
    The iskra meter's datasheet states
    "6.5.17 Dataset format
    Format is compliant with OCMF v1.0.
    Energy meter requires following fields in dataset:
    {
    "FV":"1.0",
2026-02-17 Add CF to eichrecht dataset
2026-02-20 GetEichrechtTransaction -> GetEichrechtTransactionState
2026-02-27 Add warp4 specific pp calculation
2026-03-11 Add iso15118 improvement for Ioniq 5
2026-03-23 Imrove indentation
2026-03-25 Add date and ref for 2.2.20 release
2026-03-31 Add test mode for improved provisioning
2026-05-07 Fix WARP2 breathing bug

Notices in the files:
hardware/evse-v2.kicad_pcb:
Licensed under CERN OHL v.1.1
Copyright (©) 2021, B.Nordmeyer
